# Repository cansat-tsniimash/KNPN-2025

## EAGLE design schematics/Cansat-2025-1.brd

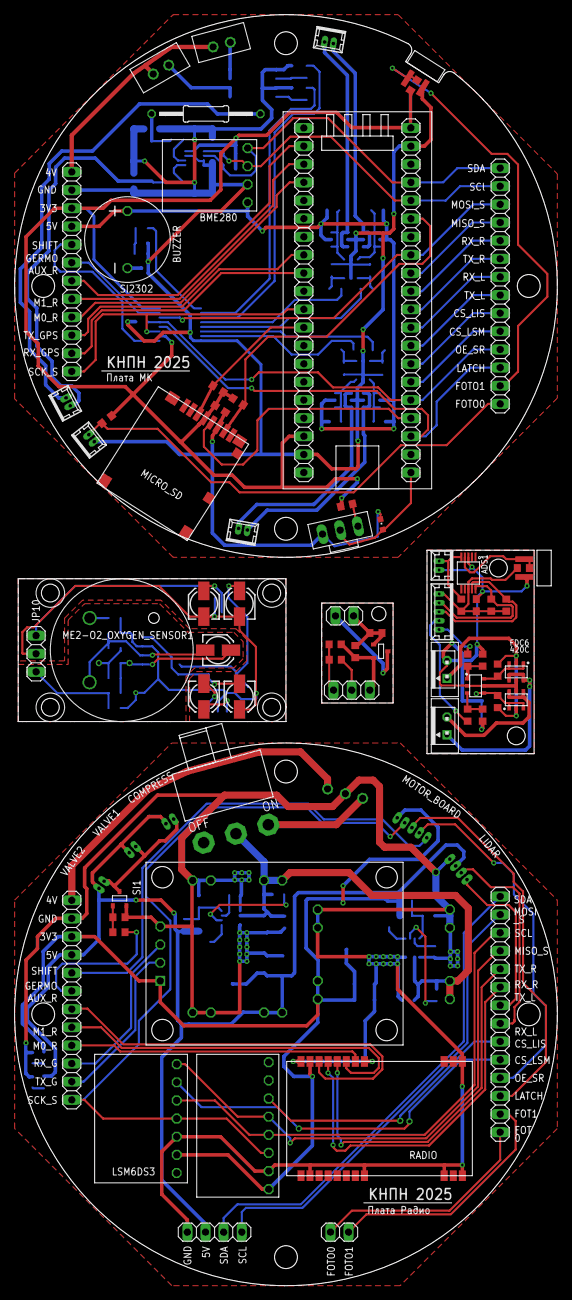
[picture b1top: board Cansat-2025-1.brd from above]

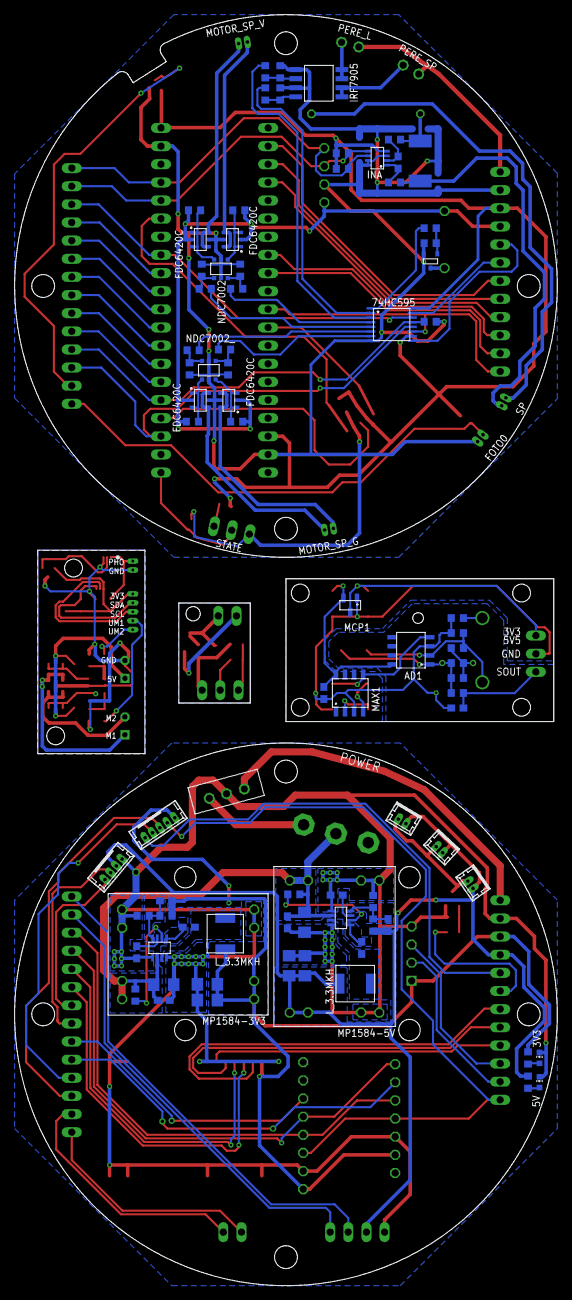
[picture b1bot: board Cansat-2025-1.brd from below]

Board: 2 copper layers, 76.0 x 178.0 mm, 152 parts (82 on the bottom side), 134 nets.

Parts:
3V3, 5V: CHIP-LED0603
74HC595: 74HC595; TSSOP16
AD1: AD8572
ADS1: ADS1115; MSOP10
BME280: BME280BME280-PINS-ONLY; BME280-PINS-ONLY
BUZZER: BUZZERS8R6; BUZZER-S8R12
C1, C25, C29: 0.1uF; C0603
C2, C5: 100nF; C0603
C3, C7, C11, C14: 0,1u; C0603
C4, C12: 0,1u; C1206
C6, C13: 22u; C0603
C8, C15: 33p; C0603
C9, C10, C16, C17: 22u; C1206
C26, C27, C28: 10uF; 153CLV-0405
C30, C31: 1uF; 153CLV-0405
COMPRESS: MOLEX-2-1.25; 53047-02
FOTO0: MOLEX-2-1.25; 53047-02
GPS-NEO7M: GPS-NEO7M
INA: INA219AID; SOT23-8
IRF7905: IRF7905PBF; SO8
JP1, JP3: 1X14
JP2, JP9: 1X02
JP4, JP5: 1X12
JP6: 1X04
JP8, JP10: 1X03
LIDAR: MOLEX-4-1.25; 53047-04
LSM6DS3: LSM6DS3; LSM6DS3_WITHOUT
L_3.3: L_3.3MKH; L_SPM5020
MAX1: MAX660
MCP1: MCP1700
ME2-O2_OXYGEN_SENSOR1: ME2-O2_OXYGEN_SENSOR
MICRO_SD: SD
MOTOR_BOARD: MOLEX-5-1.25; 53047-05
MOTOR_SP_G: MOLEX-2-1.25; 53047-02
MOTOR_SP_V: MOLEX-2-1.25; 53047-02
MP1584-3V3: MP1584-B
MP1584-5V: MP1584; MP1584-B
NDC7002, NDC7002_: NDC7002N; SOT23-6
PERE_L: JST-2-2.5
PERE_SP: JST-2-2.5
POWER: SS_12D11
R0, R18: 2k2; R0603
R1: 5K; R0603
R3: 68K; R0603
R4, R5, R56, R57, R59, R60, R66, R68: 10K; R0603
R6: 47R; R0603
R11, R16, R17, R22, R24, R26, R27, R28, R29, R32, R33, R34, R35, R41, R44, R48: 10k; R0603
R12, R23, R25, R30, R31, R36, R37, R49, R58, R65, R67: 100R; R0603
R13, R46, R47, R61, R62: 2k; R0603
R14, R15, R38: 5k1; R0603
R19, R20: 10R; R0603
R21: R05; R2512
R39: 100R; 0207/15
R40, R43: 100k; R0603
R42: 31k6; R0603
R45: 53k6; R0603
R55: 5.1K; R0603
R63, R64: 5K1; R0603
RADIO: E220-400T22S
RT2: 5K; R0603
SI1, SI2300A, SI2302: SI2302CDS; SOT23-3
SP: MOLEX-2-1.25; 53047-02
STATE: CHIPLED_0603
STM32F411: STM32F411_BOARD
U$0, U$9: VT93N1
U$1: SWITCH_MSS
U$4: Плата МК; LOGO
U$5: Плата Радио; LOGO
U$6, U$7: MP2225; TSOT23-8
U$8: L_3.3MKH; L_SPM5020
U$10: LIS3MDL
U$11: IRF5852; TSOP-6
U$12, U$13, U$19, U$20, U$21, U$22: FDC6420C; TSOP-6
VALVE1, VALVE2: MOLEX-2-1.25; 53047-02
X5: AKKUM; JST-3-2.5
X6: JST-5; MOLEX-5-1.25
X7: JST-2-1.25; MOLEX-2-1.25
X8, X9: JST-2-K-S; B2B-PH-K-S

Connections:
3.3-5.5V1: C30.+, JP10.3, MCP1.P3
3V1: 74HC595.10, 74HC595.16, C2.2, INA.4, JP4.3, MICRO_SD.VDD, R0.1, R13.2, R14.2, R15.2, R16.1, R17.1, R18.1, STM32F411.18, STM32F411.40
3V2: C8.1, C9.2, C10.2, GPS-NEO7M.P$1, JP5.3, LSM6DS3.P$2, L_3.3.P$1, MOTOR_BOARD.5, MP1584-3V3.P$7, MP1584-3V3.P$8, R42.2, R47.2, RADIO.P$25, U$10.UCC
3V3: AD1.P8, C29.1, C31.+, MAX1.P8, MCP1.P2
3V4: ADS1.8, C25.2, R61.1, R62.1, R63.2, R64.2, X6.P$1
4V: JP4.1, PERE_L.1, PERE_SP.1
4V1: JP5.1, X5.3
5V1: BME280.P$4, BUZZER.P$2, JP4.4, R26.1, R27.1, R32.1, R33.1, U$19.P$2, U$20.P$2, U$21.P$2, U$22.P$2
5V2: C15.1, C16.2, C17.2, COMPRESS.2, JP5.4, JP6.2, LIDAR.3, MP1584-5V.P$7, MP1584-5V.P$8, R45.2, R46.2, U$8.P$1, VALVE1.2, VALVE2.2
5V3: R59.2, R60.1, U$12.P$2, U$13.P$2, X8.1
-3V1: AD1.P4, C27.-, MAX1.P5
AUX_RADIO: JP4.7, STM32F411.2
AUX_RADIO1: JP5.7, RADIO.P$24
BUS+: C4.2, C6.2, C12.2, C13.2, MP1584-3V3.P$1, MP1584-3V3.P$2, MP1584-5V.P$1, MP1584-5V.P$2, POWER.2, R40.1, R43.1, U$6.P$2, U$7.P$2
BUS+_OUT: POWER.3, X5.1
BUZZER: 74HC595.1, R12.1
C1: AD1.P2, C26.-, ME2-O2_OXYGEN_SENSOR1.C, R3.1, R4.2
CK_SD: MICRO_SD.CLK, STM32F411.24
CMD_SD: MICRO_SD.CMD, R17.2, STM32F411.12
CS_LIS: JP3.9, STM32F411.27
CS_LIS1: JP1.9, U$10.CS
CS_LSM: JP3.10, STM32F411.26
CS_LSM1: JP1.10, LSM6DS3.P$6
D0_SD: MICRO_SD.DAT0, R16.2, STM32F411.35
D1: JP9.2, SI2300A.3
D2: ME2-O2_OXYGEN_SENSOR1.D, R6.2
FOTO0: FOTO0.2, JP3.14, R18.2
FOTO1: JP3.13, R0.2, U$0.P$1
FOTO2: JP1.13, JP2.1
FOTO3: JP1.14, JP2.2
G: JP9.1, R57.2, R58.1, R58.2, SI2300A.1
GERMO: 74HC595.15, JP4.6
GERMO1: JP5.6, R49.1
GND: AD1.P3, C1.2, C27.+, C29.2, C30.-, C31.-, JP10.2, MAX1.P3, MCP1.P1, R4.1, R6.1
GND1: 74HC595.8, BME280.P$3, C2.1, FOTO0.1, INA.3, INA.7, INA.8, IRF7905.1, IRF7905.3, JP4.2, MICRO_SD.VSS, NDC7002.2, NDC7002.5, NDC7002_.2, NDC7002_.5, R11.2, R22.2, R24.2, R28.1, R29.1, R34.1, R35.1, R38.1, SI2302.2, STATE.C, STM32F411.19, STM32F411.39, U$0.P$2, U$1.3, U$19.P$5, U$20.P$5, U$21.P$5, U$22.P$5
GND2: 3V3.C, 5V.C, C3.1, C4.1, C6.1, C9.1, C10.1, C11.1, C12.1, C13.1, C16.1, C17.1, GPS-NEO7M.P$4, JP5.2, JP6.1, LIDAR.4, LSM6DS3.P$3, MP1584-3V3.P$3, MP1584-3V3.P$4, MP1584-3V3.P$5, MP1584-3V3.P$6, MP1584-5V.P$3, MP1584-5V.P$4, MP1584-5V.P$5, MP1584-5V.P$6, R41.2, R44.2, R48.2, RADIO.P$2, RADIO.P$8, RADIO.P$11, RADIO.P$13, RADIO.P$14, RADIO.P$15, RADIO.P$16, RADIO.P$19, RADIO.P$26, SI1.2, U$6.P$1, U$6.P$4, U$7.P$1, U$7.P$4, U$10.GND, X5.2
GND4: JP8.3, R56.2, R57.1, SI2300A.2
GND5: ADS1.3, C25.1, R66.1, R68.1, U$9.P$2, U$11.P$2, U$11.P$5, U$12.P$5, U$13.P$5, X7.P$2, X8.2
IN: JP8.2, R55.1
INA_SP+: R20.1, R21.1, R39.1
LATCH_SR: 74HC595.12, JP3.12, STM32F411.23
LATCH_SR1: JP1.12, MOTOR_BOARD.3
M0_RADIO: JP4.9, STM32F411.4
M0_RADIO1: JP5.9, RADIO.P$20
M1_RADIO: JP4.8, STM32F411.3
M1_RADIO1: JP5.8, RADIO.P$21
M3: U$12.P$4, U$12.P$6, X9.2
M4: U$13.P$4, U$13.P$6, X9.1
MISO_SENS: JP3.4, STM32F411.32
MISO_SENS1: JP1.4, LSM6DS3.P$7, U$10.SDO
MK_MOTOR1+: 74HC595.4, R37.1
MK_MOTOR1-: 74HC595.5, R36.1
MK_MOTOR2+: 74HC595.6, R31.1
MK_MOTOR2-: 74HC595.7, R30.1
MOSI_SENS: 74HC595.14, JP3.3, STM32F411.33
MOSI_SENS1: JP1.3, LSM6DS3.P$5, U$10.SDA
MOTOR1+: MOTOR_SP_V.1, U$22.P$4, U$22.P$6
MOTOR1-: MOTOR_SP_V.2, U$21.P$4, U$21.P$6
MOTOR2+: MOTOR_SP_G.1, U$20.P$4, U$20.P$6
MOTOR2-: MOTOR_SP_G.2, U$19.P$4, U$19.P$6
unnamed: AD1.P1, C26.+, R1.1, R5.2, RT2.1
unnamed: R13.1, U$1.1
unnamed: C8.2, R41.1, R42.1, U$6.P$8
unnamed: R1.2, R3.2, RT2.2
unnamed: C28.+, MAX1.P2
unnamed: C11.2, U$7.P$7
unnamed: R43.2, U$7.P$6
unnamed: C15.2, R44.1, R45.1, U$7.P$8
unnamed: C3.2, U$6.P$7
unnamed: R40.2, U$6.P$6
unnamed: C7.2, U$6.P$5
unnamed: C7.1, L_3.3.P$2, U$6.P$3
unnamed: BUZZER.P$1, SI2302.3
unnamed: R11.1, R12.2, SI2302.1
unnamed: C5.2, INA.2, R20.2
unnamed: C14.2, U$7.P$5
unnamed: C14.1, U$7.P$3, U$8.P$2
unnamed: C5.1, INA.1, R19.2
unnamed: 5V.A, R46.1
unnamed: IRF7905.7, IRF7905.8, PERE_L.2
unnamed: IRF7905.5, IRF7905.6, PERE_SP.2
unnamed: IRF7905.2, R22.1, R23.2
unnamed: IRF7905.4, R24.1, R25.2
unnamed: NDC7002.6, R32.2, U$21.P$1, U$21.P$3
unnamed: NDC7002_.6, R26.2, U$19.P$1, U$19.P$3
unnamed: NDC7002_.4, R27.2, U$20.P$1, U$20.P$3
unnamed: NDC7002.4, R33.2, U$22.P$1, U$22.P$3
unnamed: NDC7002.1, R34.2, R36.2
unnamed: NDC7002.3, R35.2, R37.2
unnamed: 3V3.A, R47.1
unnamed: R48.1, R49.2, SI1.1
unnamed: NDC7002_.1, R28.2, R30.2
unnamed: COMPRESS.1, SI1.3, VALVE1.1, VALVE2.1
unnamed: NDC7002_.3, R29.2, R31.2
unnamed: ADS1.4, R61.2, U$9.P$1
unnamed: R65.1, R66.2, U$11.P$1
unnamed: R67.2, R68.2, U$11.P$3
unnamed: C28.-, MAX1.P4
OE_SR: 74HC595.13, JP3.11, R38.2, STM32F411.25
OE_SR1: JP1.11, MOTOR_BOARD.2
OUT: JP8.1, R55.2, R56.1
PERE1: 74HC595.3, R23.1
PERE2: 74HC595.2, R25.1
PHOTO1: ADS1.5, R62.2, X7.P$1
RX_GPS: JP4.11, STM32F411.9
RX_GPS1: GPS-NEO7M.P$3, JP5.10
RX_LIDAR: JP3.7, STM32F411.29
RX_LIDAR1: JP1.8, LIDAR.2
RX_RADIO: JP3.5, STM32F411.31
RX_RADIO1: JP1.6, RADIO.P$23
SCK_SENS: 74HC595.11, JP4.12, STM32F411.11
SCK_SENS1: JP5.12, LSM6DS3.P$4, MOTOR_BOARD.4, U$10.SCL
SCL1: BME280.P$2, INA.5, JP3.2, R15.1, STM32F411.36
SCL2: JP1.2, JP6.4
SCL3: ADS1.9, R63.1, X6.P$3
SDA1: BME280.P$1, INA.6, JP3.1, R14.1, STM32F411.37
SDA2: JP1.1, JP6.3
SDA3: ADS1.10, R64.1, X6.P$2
SHIFT: 74HC595.9, JP4.5
SHIFT1: JP5.5, MOTOR_BOARD.1
SOUT1: C1.1, JP10.1, R5.1
SP+: R19.1, R21.2, SP.1
SP-: R39.2, SP.2
SWITCH: STATE.A, STM32F411.21, U$1.2
TX_GPS: JP4.10, STM32F411.8
TX_GPS1: GPS-NEO7M.P$2, JP5.11
TX_LIDAR: JP3.8, STM32F411.28
TX_LIDAR1: JP1.7, LIDAR.1
TX_RADIO: JP3.6, STM32F411.30
TX_RADIO1: JP1.5, RADIO.P$22
UM1_MOSFET1: R59.1, U$11.P$6, U$13.P$1, U$13.P$3
UM2_MOSFET1: R60.2, U$11.P$4, U$12.P$1, U$12.P$3
UM3: R67.1, X6.P$4
UM4: R65.2, X6.P$5

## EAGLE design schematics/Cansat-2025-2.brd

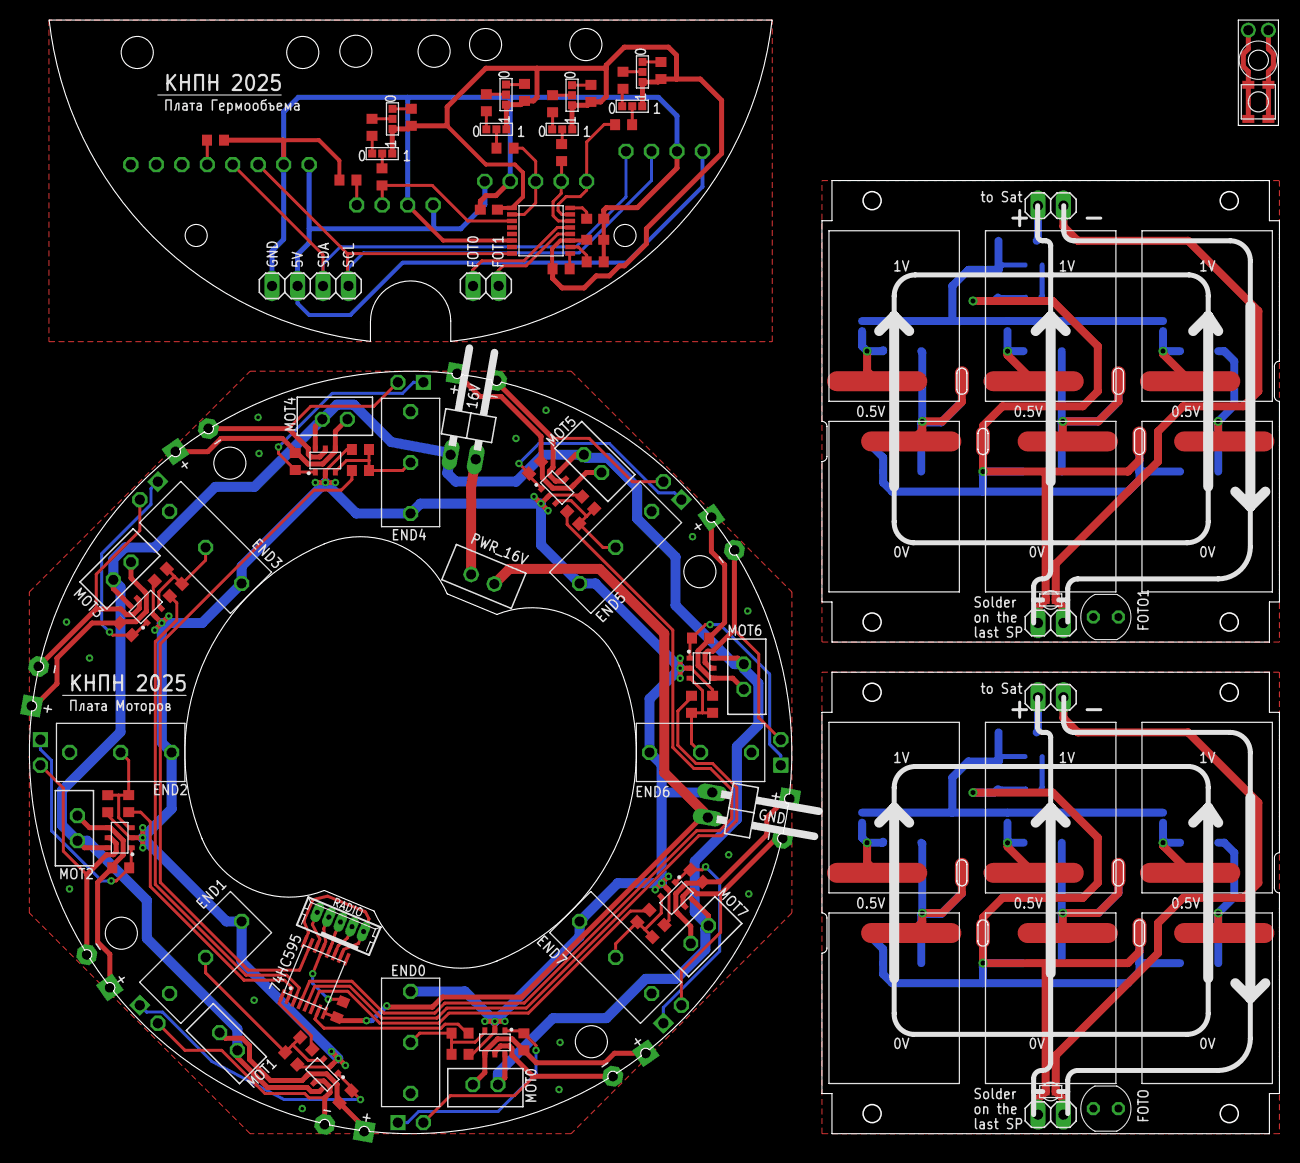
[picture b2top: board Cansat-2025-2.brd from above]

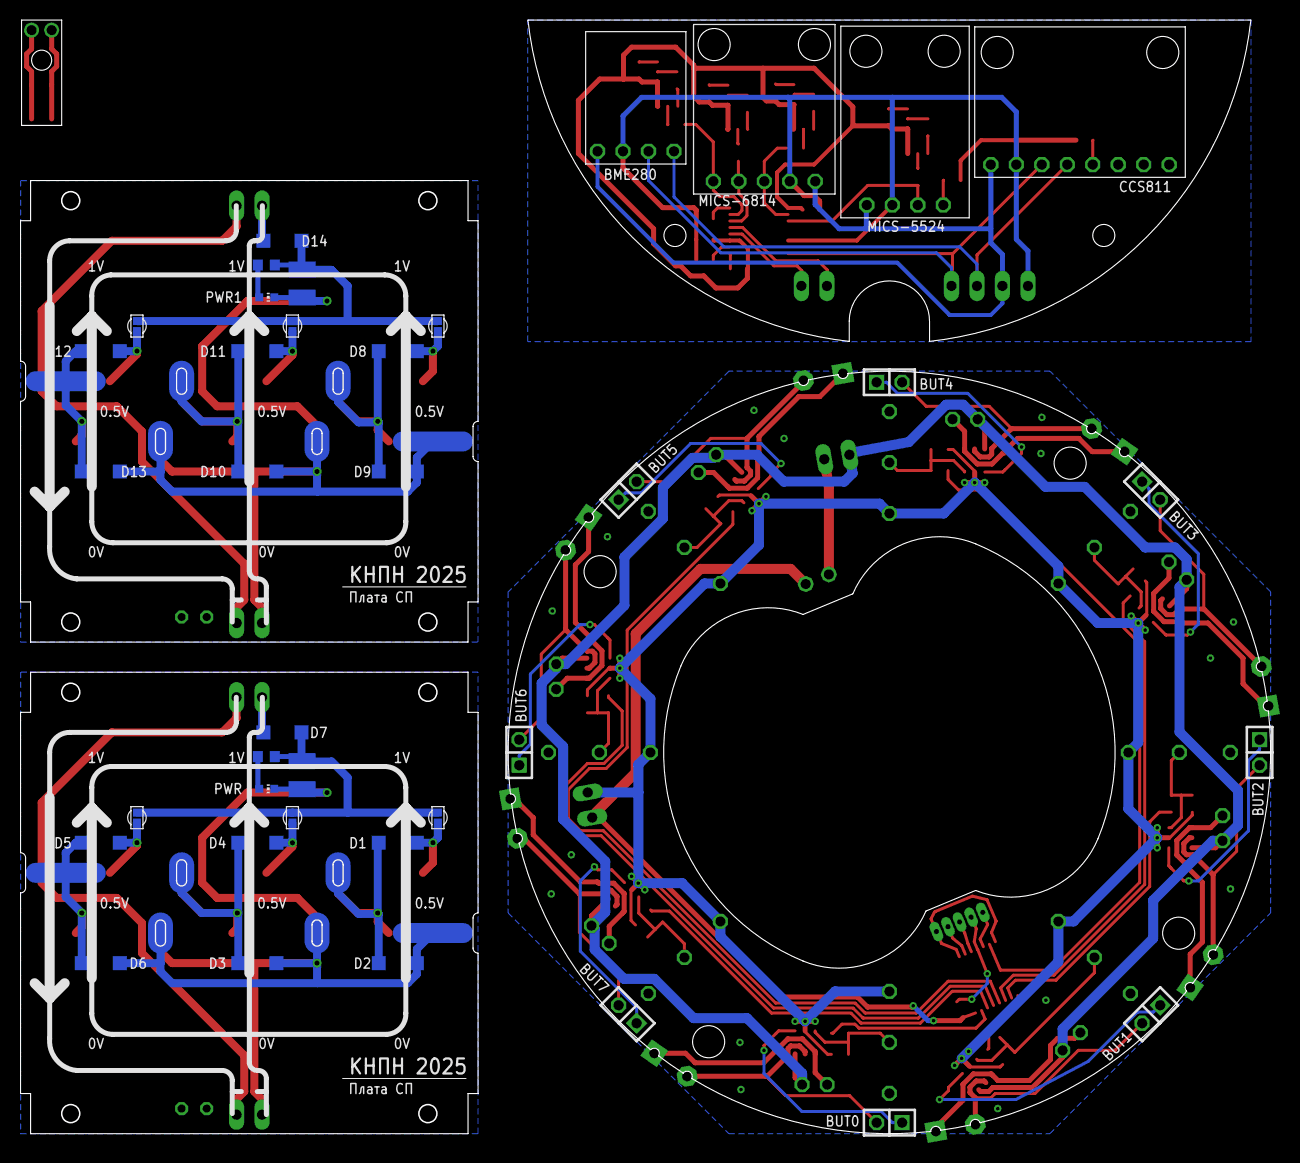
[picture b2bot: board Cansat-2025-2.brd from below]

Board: 2 copper layers, 124.6 x 111.0 mm, 155 parts (40 on the bottom side), 105 nets.

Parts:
16V: 1X02/90
74HC595: 74HC595; TSSOP16
BME280: BME280BME280-PINS-ONLY; BME280-PINS-ONLY
BUT0, BUT1, BUT2, BUT3, BUT4, BUT5, BUT6, BUT7: 1X02
C1, C2: 47u; C1210
C3, C4, C5: 100nF; C0603
CCS811: CCS811; CSS811
D1, D2, D3, D4, D5, D6, D7, D8, D9, D10, D11, D12, D13, D14: MBR0520LT; SOD123
END0, END1, END2, END3, END4, END5, END6, END7: CONCEVIC
FOTO, FOTO1: VT93N1VERT; VT93N1-VERT
GND: 1X02/90
JP1, JP2, JP4: 1X02
JP3: 1X04
MICS-5524: MICS_5524; MICS-5524
MICS-6814: MICS-6814
MOT0, MOT1, MOT2, MOT3, MOT4, MOT5, MOT6, MOT7: JST-2-2.5
PWR, PWR1: CHIP-LED0603
PWR_16V: JST-2-2.5
R1, R2: 2k7; R0603
R3, R6, R9, R12, R16, R19, R22, R25: 100R; R0603
R4, R5, R7, R8, R10, R11, R13, R15, R17, R18, R20, R21, R23, R24, R26, R27, R29, R30, R31, R33: 10k; R0603
R14, R28, R32, R34, R35: 5k1; R0603
R39, R41, R43, R45: 100k; R0603
R40, R42, R44, R46: 1M; R0603
RADIO: MOLEX-5-1.25; 53047-05
SP-OUT, SP-OUT1: 1X02
U$1, U$3, U$4, U$8, U$12, U$14, U$15, U$19: SOLAR-2_INVERT0-2; SOLAR_0-2_INVERT
U$2, U$6, U$13, U$18: SOLAR-2_INVERT1-2; SOLAR_1-2_INVERT
U$5, U$17: Плата СП; LOGO
U$7, U$9, U$10, U$11, U$16, U$20, U$21, U$22: VIAS-CONNECT
U$23: Плата Моторов; LOGO
U$24, U$25, U$26, U$27, U$28, U$29, U$30, U$32: IRF5852; TSOP-6
U$31, U$33, U$34, U$44, U$45, U$46, U$47, U$48: CONNECT_3
U$35, U$36, U$37, U$38, U$39, U$40, U$41, U$42: CONTACT_SIDE_4MM_2PIN
U$43: Плата Гермообъема; LOGO
U$49: AD5593
U$50: BTN_VERY_SMALLCUT; BTN-VS-CUT

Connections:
3V1: C4.1, C5.1, R35.2, R40.1, R42.1, R44.1, R46.1, U$31.1, U$33.1, U$34.1, U$44.1, U$45.1, U$46.1, U$47.1, U$48.1, U$49.P$3, U$49.P$9
3V3: 74HC595.10, 74HC595.16, RADIO.1
5V: BME280.P$4, CCS811.P$1, JP3.2, MICS-5524.P$4, MICS-6814.P$1
16V_IN: 16V.1, MOT0.1, MOT1.1, MOT2.1, MOT3.1, MOT4.1, MOT5.1, MOT6.1, MOT7.1, U$24.P$6, U$25.P$6, U$26.P$6, U$27.P$6, U$28.P$6, U$29.P$6, U$30.P$6, U$32.P$6
16V_OUT: 16V.2, PWR_16V.1
CO: MICS-6814.P$5, R33.2, U$49.P$7
EN: MICS-5524.P$1, R32.1
FOTO0: JP4.2, U$49.P$5
FOTO1: JP4.1, U$49.P$4
GND: BME280.P$3, C3.2, C4.2, C5.2, CCS811.P$2, JP3.1, MICS-5524.P$3, MICS-6814.P$2, R28.2, R32.2, R34.2, U$49.P$14
GND_IN: END0.P$1, END1.P$1, END2.P$1, END3.P$1, END4.P$1, END5.P$1, END6.P$1, END7.P$1, GND.1, R4.2, R7.2, R10.2, R13.2, R17.2, R20.2, R23.2, R26.2, U$24.P$2, U$25.P$2, U$26.P$2, U$27.P$2, U$28.P$2, U$29.P$2, U$30.P$2, U$32.P$2
GND_OUT: 74HC595.8, GND.2, PWR_16V.2, R14.1
LATCH_SR: 74HC595.12, RADIO.3
MICS: MICS-5524.P$2, R31.2, U$49.P$11
MOTOR0: 74HC595.7, R3.1
MOTOR1: 74HC595.1, R6.1
MOTOR2: 74HC595.2, R9.1
MOTOR3: 74HC595.3, R12.1
MOTOR4: 74HC595.15, R16.1
MOTOR5: 74HC595.4, R19.1
MOTOR6: 74HC595.5, R22.1
MOTOR7: 74HC595.6, R25.1
unnamed: D7.A, JP1.2
unnamed: D5.A, U$6.IN-2, U$11.1
unnamed: D4.A, U$4.IN-2, U$10.1
unnamed: PWR.A, R1.2
unnamed: D1.C, D2.A, U$1.OUT-2, U$1.OUT-21, U$2.IN-2
unnamed: D3.A, D4.C, U$3.IN-2, U$4.OUT-2, U$4.OUT-21
unnamed: D1.A, U$1.IN-2, U$9.1
unnamed: D5.C, D6.A, U$6.OUT, U$8.IN-2
unnamed: PWR1.A, R2.2
unnamed: D12.C, D13.A, U$18.OUT, U$19.IN-2
unnamed: D14.A, JP2.2
unnamed: D8.C, D9.A, U$12.OUT-2, U$12.OUT-21, U$13.IN-2
unnamed: D11.A, U$15.IN-2, U$21.1
unnamed: D12.A, U$18.IN-2, U$22.1
unnamed: D8.A, U$12.IN-2, U$20.1
unnamed: D10.A, D11.C, U$14.IN-2, U$15.OUT-2, U$15.OUT-21
unnamed: MOT0.2, R5.1, U$24.P$4, U$38.P$1
unnamed: END0.P$2, R3.2, R4.1, U$24.P$3
unnamed: END1.P$2, R6.2, R7.1, U$25.P$3
unnamed: END2.P$2, R9.2, R10.1, U$26.P$3
unnamed: BUT0.2, U$24.P$5, U$38.P$2
unnamed: BUT0.1, R5.2, U$24.P$1
unnamed: BUT1.2, U$25.P$5, U$35.P$2
unnamed: BUT1.1, R8.1, U$25.P$1
unnamed: MOT1.2, R8.2, U$25.P$4, U$35.P$1
unnamed: MOT2.2, R11.2, U$26.P$4, U$36.P$1
unnamed: BUT2.2, U$26.P$5, U$36.P$2
unnamed: BUT2.1, R11.1, U$26.P$1
unnamed: END3.P$2, R12.2, R13.1, U$27.P$3
unnamed: MOT3.2, R15.2, U$27.P$4, U$37.P$1
unnamed: BUT3.2, U$27.P$5, U$37.P$2
unnamed: BUT3.1, R15.1, U$27.P$1
unnamed: END4.P$2, R16.2, R17.1, U$28.P$3
unnamed: MOT4.2, R18.2, U$28.P$4, U$39.P$1
unnamed: BUT4.2, U$28.P$5, U$39.P$2
unnamed: BUT4.1, R18.1, U$28.P$1
unnamed: END5.P$2, R19.2, R20.1, U$29.P$3
unnamed: MOT5.2, R21.2, U$29.P$4, U$40.P$1
unnamed: BUT5.2, U$29.P$5, U$40.P$2
unnamed: BUT5.1, R21.1, U$29.P$1
unnamed: END6.P$2, R22.2, R23.1, U$30.P$3
unnamed: MOT6.2, R24.2, U$30.P$4, U$41.P$1
unnamed: BUT6.2, U$30.P$5, U$41.P$2
unnamed: BUT6.1, R24.1, U$30.P$1
unnamed: END7.P$2, R25.2, R26.1, U$32.P$3
unnamed: MOT7.2, R27.2, U$32.P$4, U$42.P$1
unnamed: BUT7.2, U$32.P$5, U$42.P$2
unnamed: BUT7.1, R27.1, U$32.P$1
unnamed: R39.2, U$44.3
unnamed: R33.1, U$44.2
unnamed: R40.2, U$45.3
unnamed: R39.1, U$45.2
unnamed: R41.2, U$46.3
unnamed: R29.1, U$46.2
unnamed: R42.2, U$47.3
unnamed: R41.1, U$47.2
unnamed: R43.2, U$48.3
unnamed: R30.1, U$48.2
unnamed: R44.2, U$31.3
unnamed: R43.1, U$31.2
unnamed: R45.2, U$33.3
unnamed: R31.1, U$33.2
unnamed: R46.2, U$34.3
unnamed: R45.1, U$34.2
unnamed: C3.1, U$49.P$8
unnamed: R34.1, U$49.P$2
unnamed: R35.1, U$49.P$1
NH3: MICS-6814.P$4, R30.2, U$49.P$6
NO2: MICS-6814.P$3, R29.2, U$49.P$10
OE_SR: 74HC595.13, R14.2, RADIO.4
P1: U$50.P$1, U$50.P$2
P2: U$50.P$3, U$50.P$4
SCK_SENS: 74HC595.11, RADIO.2
SCL: BME280.P$2, CCS811.P$3, JP3.4, U$49.P$16
SDA: BME280.P$1, CCS811.P$4, JP3.3, U$49.P$15
SHIFT: 74HC595.14, RADIO.5
SP+: C1.1, D7.C, R1.1, U$9.2, U$10.2, U$11.2
SP+1: C2.1, D14.C, R2.1, U$20.2, U$21.2, U$22.2
SP+-: C1.2, D2.C, D3.C, D6.C, PWR.C, SP-OUT.1, U$2.OUT, U$3.OUT-2, U$3.OUT-21, U$7.1, U$8.OUT-2, U$8.OUT-21
SP+-1: C2.2, D9.C, D10.C, D13.C, PWR1.C, SP-OUT1.1, U$13.OUT, U$14.OUT-2, U$14.OUT-21, U$16.1, U$19.OUT-2, U$19.OUT-21
SP-: JP1.1, SP-OUT.2, U$7.2
SP-1: JP2.1, SP-OUT1.2, U$16.2
WAC: CCS811.P$5, R28.1

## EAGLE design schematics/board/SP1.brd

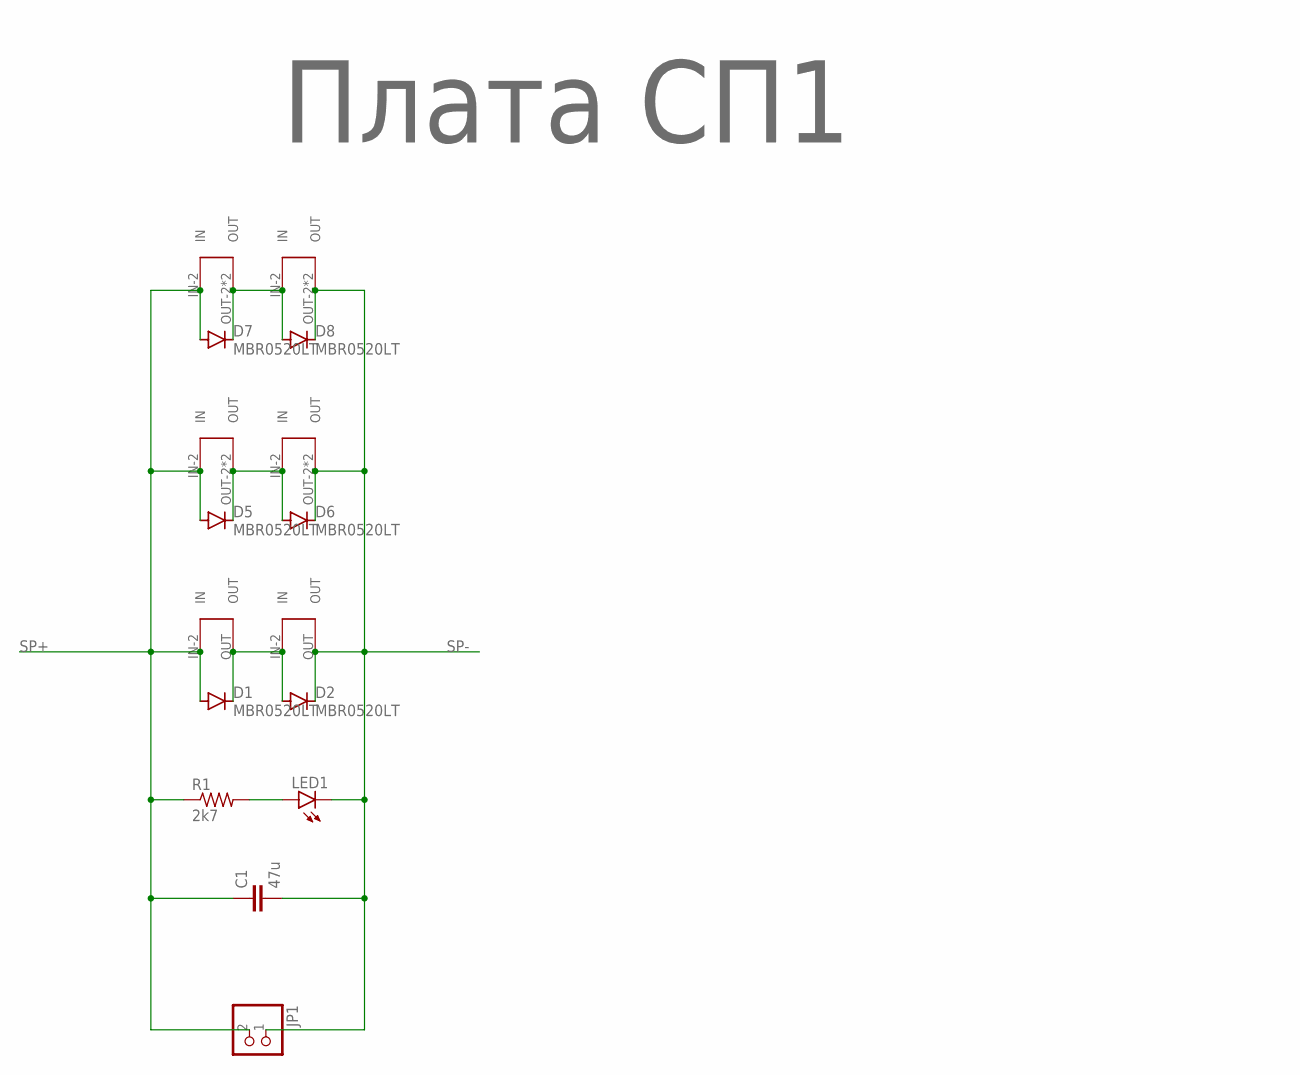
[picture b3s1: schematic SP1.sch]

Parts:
C1: 47u; C1210
D1, D2, D5, D6, D7, D8: MBR0520LT; SOD123
JP1: PINHD-1X2; 1X02
LED1: LEDCHIP-LED0603; CHIP-LED0603
R1: 2k7; R0603
U$1, U$2: SOLAR-2_1; SOLAR_1-2
U$3: Плата СП1; LOGO
U$5, U$6, U$7, U$8: SOLAR-2_0; SOLAR_0-2

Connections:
unnamed: D1.C, D2.A, U$1.OUT, U$2.IN-2 (IN)
unnamed: LED1.A, R1.2
unnamed: D5.C, D6.A, U$5.OUT-2 (OUT), U$5.OUT-21 (OUT), U$6.IN-2 (IN)
unnamed: D7.C, D8.A, U$7.OUT-2 (OUT), U$7.OUT-21 (OUT), U$8.IN-2 (IN)
SP+: C1.1, D1.A, D5.A, D7.A, JP1.2, R1.1, U$1.IN-2 (IN), U$5.IN-2 (IN), U$7.IN-2 (IN)
SP-: C1.2, D2.C, D6.C, D8.C, JP1.1, LED1.C, U$2.OUT, U$6.OUT-2 (OUT), U$6.OUT-21 (OUT), U$8.OUT-2 (OUT), U$8.OUT-21 (OUT)

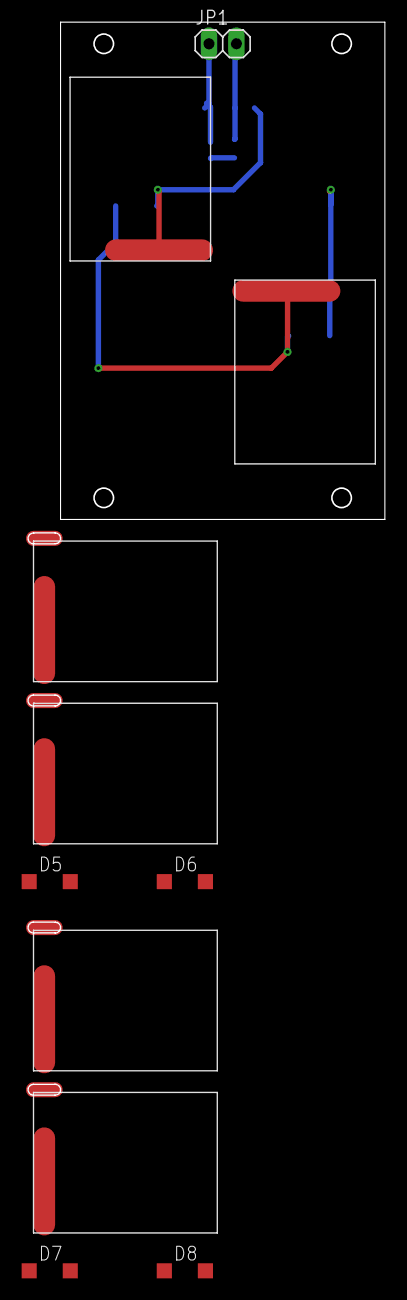
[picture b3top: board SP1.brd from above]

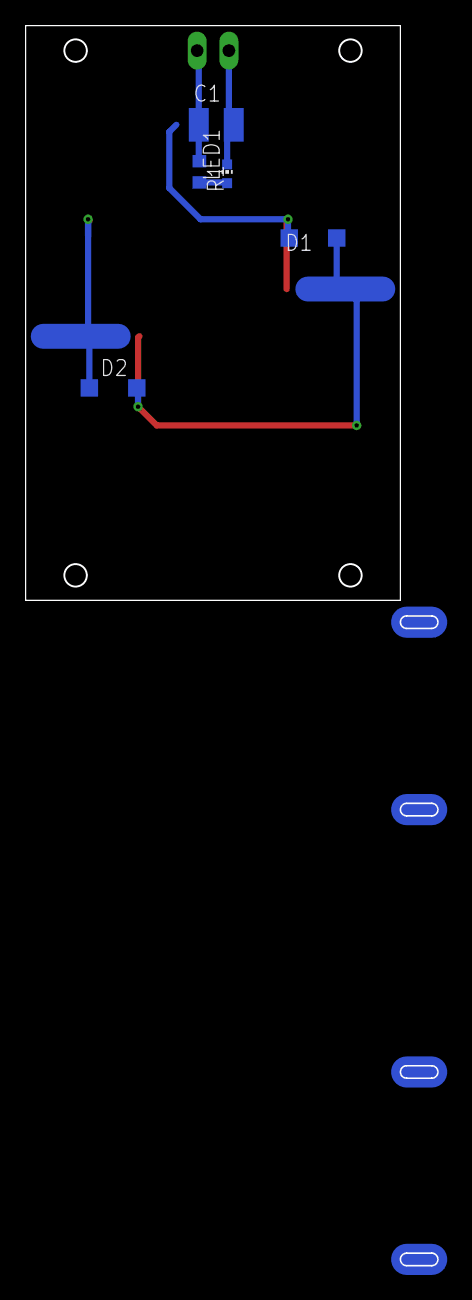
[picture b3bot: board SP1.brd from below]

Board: 2 copper layers, 33.0 x 99.2 mm, 17 parts (5 on the bottom side), 6 nets.

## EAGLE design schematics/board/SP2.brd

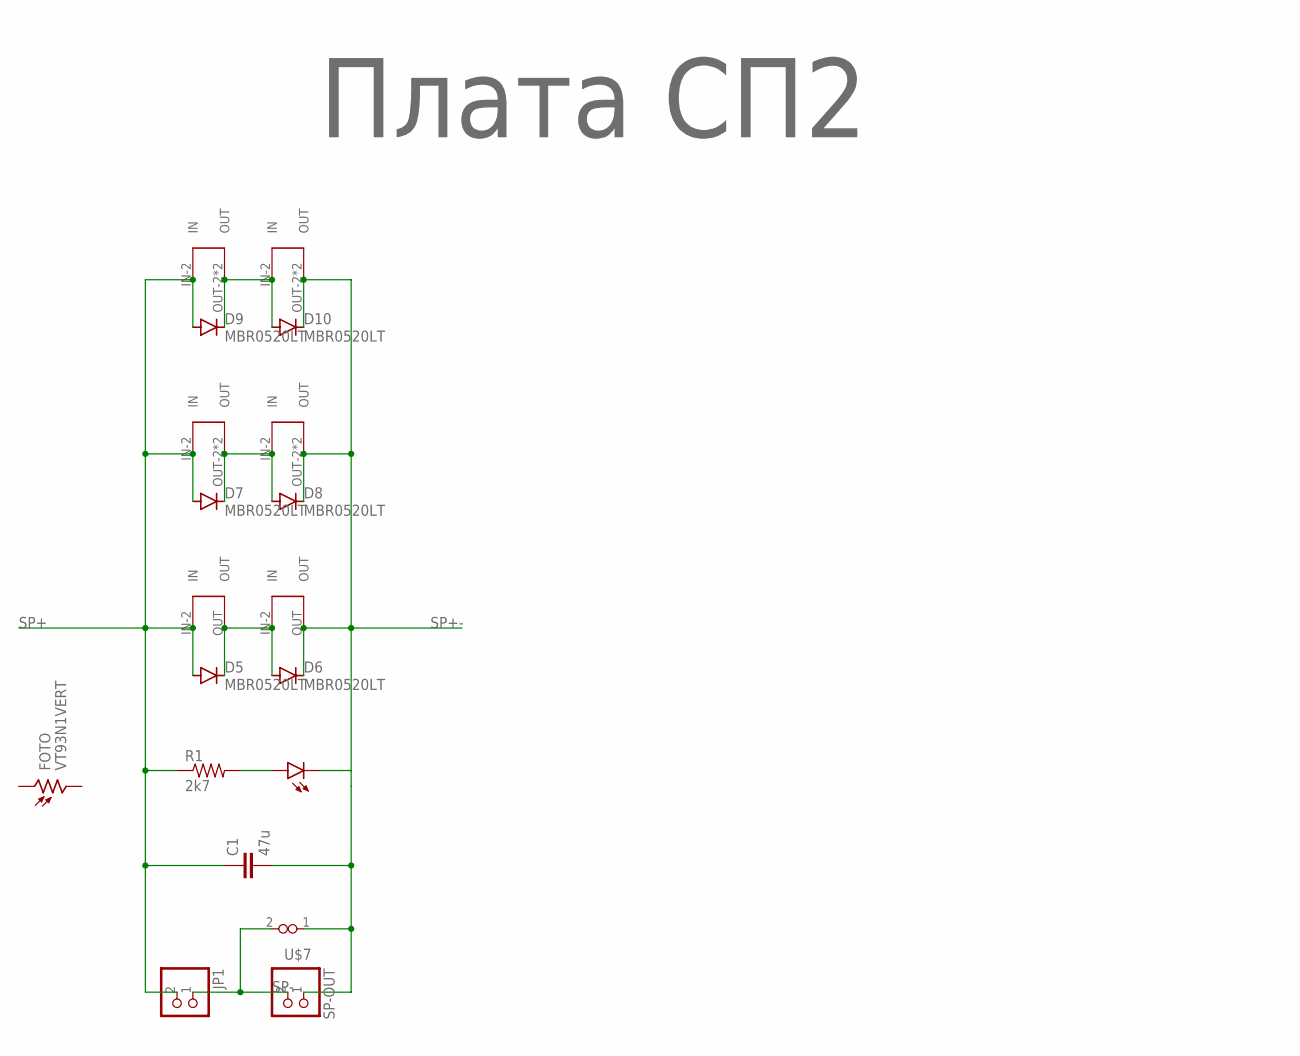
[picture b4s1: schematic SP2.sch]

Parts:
C1: 47u; C1210
D5, D6, D7, D8, D9, D10: MBR0520LT; SOD123
FOTO: VT93N1VERT; VT93N1-VERT
JP1: PINHD-1X2; 1X02
PWR: LEDCHIP-LED0603; CHIP-LED0603
R1: 2k7; R0603
SP-OUT: PINHD-1X2; 1X02
U$1: Плата СП2; LOGO
U$5, U$6: SOLAR-2_1; SOLAR_1-2
U$7: VIAS-CONNECT
U$8, U$9, U$10, U$11: SOLAR-2_0; SOLAR_0-2

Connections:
unnamed: PWR.A, R1.2
unnamed: D5.C, D6.A, U$5.OUT, U$6.IN-2 (IN)
unnamed: D7.C, D8.A, U$8.OUT-2 (OUT), U$8.OUT-21 (OUT), U$9.IN-2 (IN)
unnamed: D9.C, D10.A, U$10.OUT-2 (OUT), U$10.OUT-21 (OUT), U$11.IN-2 (IN)
SP+: C1.1, D5.A, D7.A, D9.A, JP1.2, R1.1, U$5.IN-2 (IN), U$8.IN-2 (IN), U$10.IN-2 (IN)
SP+-: C1.2, D6.C, D8.C, D10.C, PWR.C, SP-OUT.1, U$6.OUT, U$7.1, U$9.OUT-2 (OUT), U$9.OUT-21 (OUT), U$11.OUT-2 (OUT), U$11.OUT-21 (OUT)
SP-: JP1.1, SP-OUT.2, U$7.2

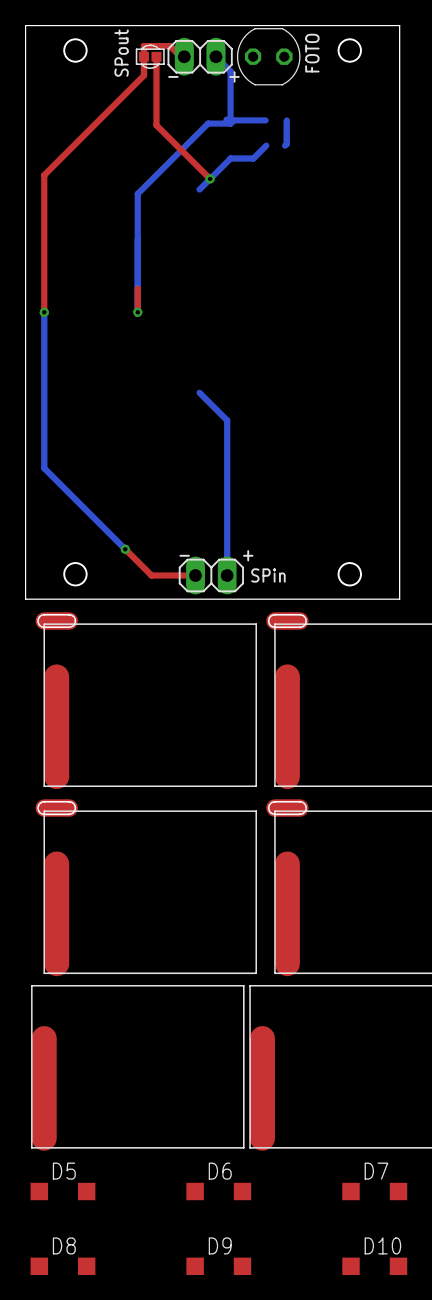
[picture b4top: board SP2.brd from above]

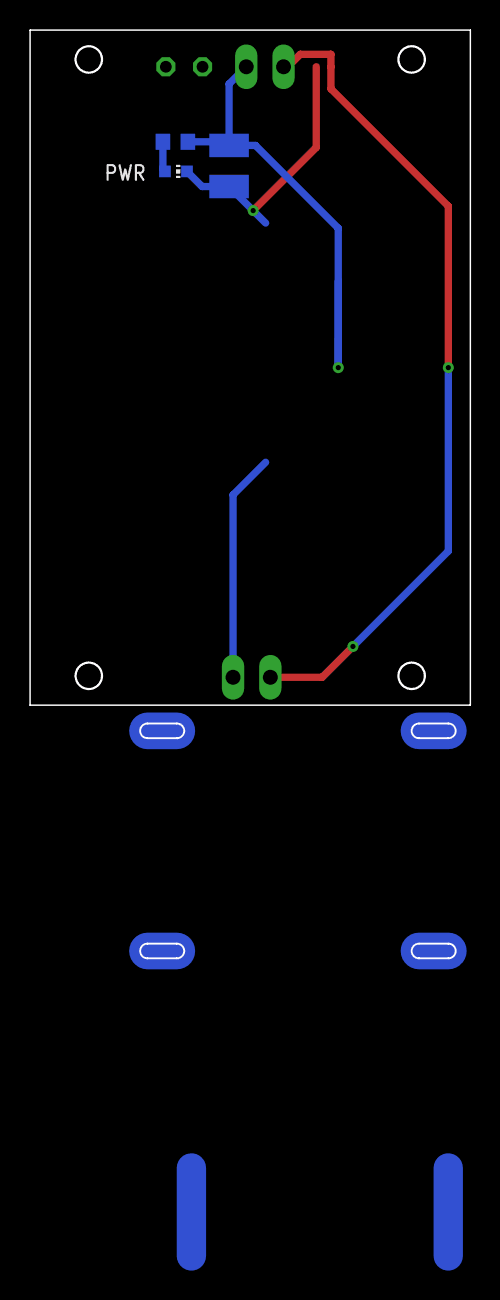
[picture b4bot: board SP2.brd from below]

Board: 2 copper layers, 20 parts (3 on the bottom side), 7 nets.
